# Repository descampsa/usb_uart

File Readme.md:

Isolated uart-usb converter.

Features:
- Silab CP2102N converter
- MAX12931 isolators
- Up to 3Mbaud UART, with hardware flow control (RTS/CTS)
- Supports 5V, 3.3V and 1.8V VCC
- Maximum withstand isolation voltage (VISO) : 3KV RMS
- Maximum working isolation voltage (VIOWM) : 445V RMS
- ABS plastic enclosure, with micro usb connector, and 0.1'' 6 pins header for uart

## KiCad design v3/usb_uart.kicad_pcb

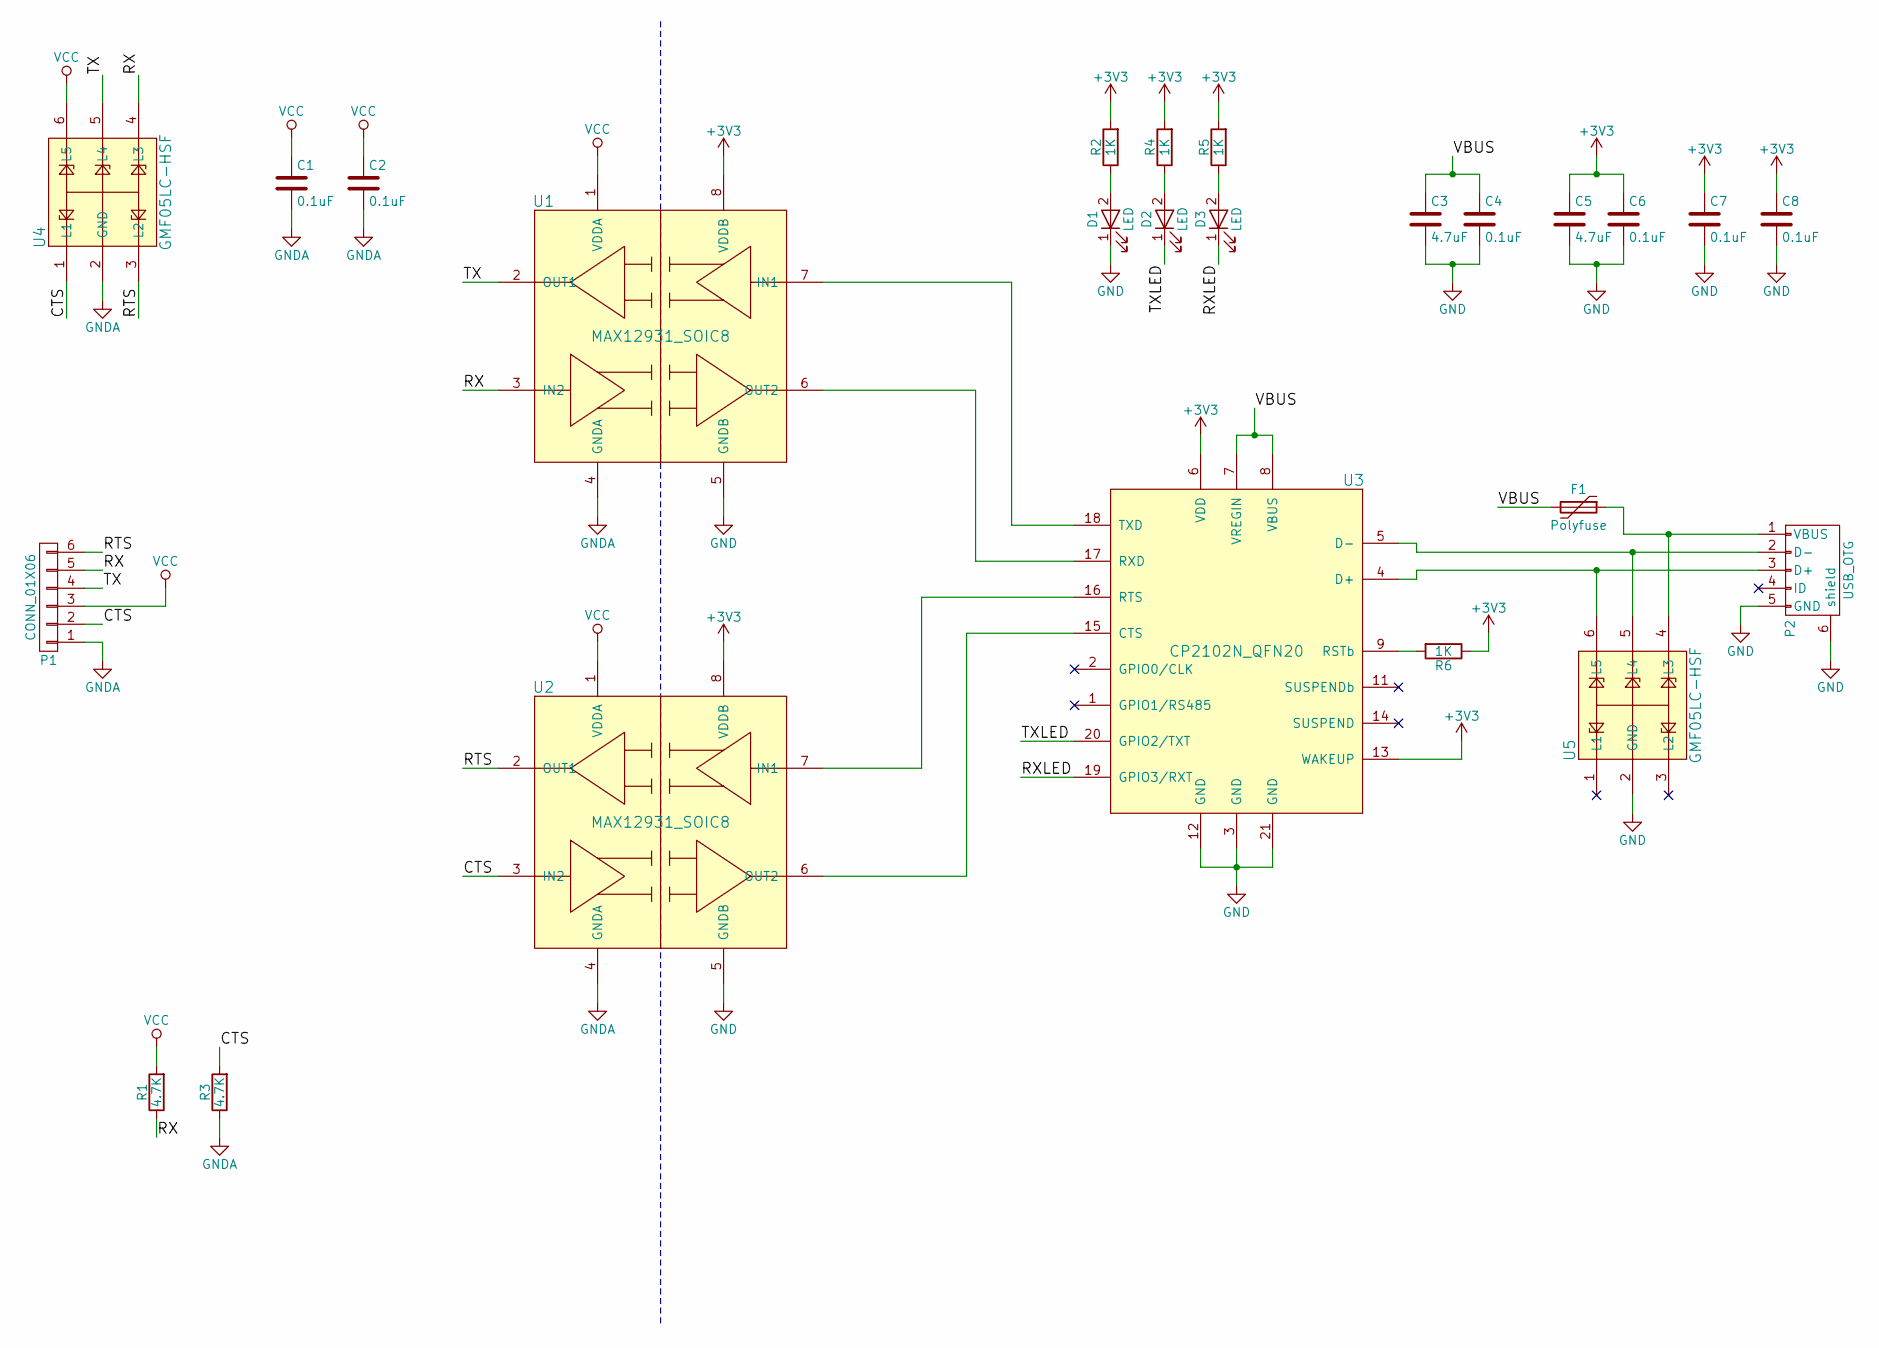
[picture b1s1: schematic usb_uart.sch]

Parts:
C1, C2, C4, C6, C7, C8: 0.1uF; C_0603
C3, C5: 4.7uF; C_0603
D1, D2, D3: LED; LED_0603
F1: Polyfuse; fuse_1206
P1: CONN_01X06; Pin_Header_Angled_1x06_Pitch2.54mm
P2: USB_OTG; ZX62D-B-5PA8
R1, R3: 4.7K; R_0603
R2, R4, R5, R6: 1K; R_0603
U1, U2: MAX12931_SOIC8; SOIC-8_3.9x4.9mm_Pitch1.27mm
U3: CP2102N_QFN20; QFN-20-1EP_3x3mm_Pitch0.5mm
U4, U5: GMF05LC-HSF; LLP75-6L

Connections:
+3V3: C5.1, C6.1, C7.1, C8.1, R2.2, R4.2, R5.2, R6.1, U1.8 (VDDB), U2.8 (VDDB), U3.6 (VDD), U3.13 (WAKEUP)
/CTS: P1.2, R3.2, U2.3 (IN2), U4.1 (L1)
/RTS: P1.6, U2.2 (OUT1), U4.3 (L2)
/RX: P1.5, R1.1, U1.3 (IN2), U4.4 (L3)
/RXLED: D3.1 (K), U3.19 (GPIO3/RXT)
/TX: P1.4, U1.2 (OUT1), U4.5 (L4)
/TXLED: D2.1 (K), U3.20 (GPIO2/TXT)
/VBUS: C3.1, C4.1, F1.2, U3.7 (VREGIN), U3.8 (VBUS)
GND: C3.2, C4.2, C5.2, C6.2, C7.2, C8.2, D1.1 (K), P2.5 (GND), P2.6 (shield), U1.5 (GNDB), U2.5 (GNDB), U3.3 (GND), U3.12 (GND), U3.21 (GND), U5.2 (GND)
GNDA: C1.2, C2.2, P1.1, R3.1, U1.4 (GNDA), U2.4 (GNDA), U4.2 (GND)
unnamed: D1.2 (A), R2.1
unnamed: D2.2 (A), R4.1
unnamed: D3.2 (A), R5.1
unnamed: F1.1, P2.1 (VBUS), U5.4 (L3)
unnamed: P2.2 (D-), U3.5 (D-), U5.5 (L4)
unnamed: P2.3 (D+), U3.4 (D+), U5.6 (L5)
unnamed: R6.2, U3.9 (RSTb)
unnamed: U1.6 (OUT2), U3.17 (RXD)
unnamed: U1.7 (IN1), U3.18 (TXD)
unnamed: U2.6 (OUT2), U3.15 (CTS)
unnamed: U2.7 (IN1), U3.16 (RTS)
VCC: C1.1, C2.1, P1.3, R1.2, U1.1 (VDDA), U2.1 (VDDA), U4.6 (L5)

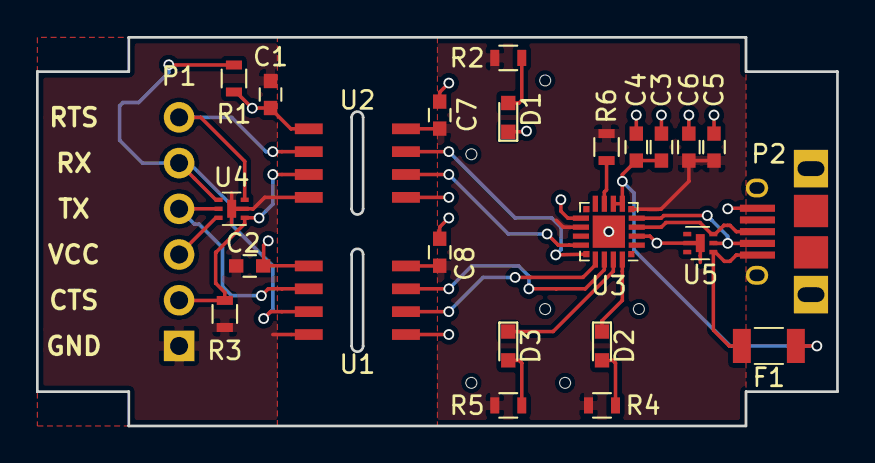
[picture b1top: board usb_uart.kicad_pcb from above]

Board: 2 copper layers, 44.5 x 21.6 mm, 25 parts (0 on the bottom side), 22 nets.
